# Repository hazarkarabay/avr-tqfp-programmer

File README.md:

Program TQFP AVR's easily without soldering
=====================

So, you designed a board that incorporates a SMD AVR and forgot to break out ISP pins. How you gonna upload your code/(if you have serial pins available)bootloader on your microcontroller?

This was my problem. Instead of adding test points to relevant signals, reordering PCBs and messing with pogo pins, I preprogrammed the chips using a TQFP adapter. Here's how I do it.

### You'll need:
- An AVR ISP programmer. You can use a dedicated programmer (Atmel MKII, Atmel ICE3, USBasp etc.) or you can use an Arduino as ISP. If you are not sure, read here: https://learn.sparkfun.com/tutorials/installing-an-arduino-bootloader
- A TQFP to DIP adapter. [I'm using this.](https://www.aliexpress.com/item/Free-shipping-Chip-programmer-TQFP32-QFP32-LQFP32-TO-DIP28-adapter-socket-support-ATMEGA8-series-TL866A-TL866CS/1969735009.html?aff_platform=ae-aff-deeplink&cpt=1499865009701&sk=UznmeyJee&aff_trace_key=a9dd8dea9e4f4ac5bc85a772afb82508-1499865009701-08514-UznmeyJee)
- ISP to TQFP-DIP adapter board. This board goes between your ISP programmer and TQFP adapter. You can get the adapter board from [pcbs.io](https://PCBs.io/share/r1D3D) or make the board with files provided in this repo and using your favorite method (toner transfer, photoresist etc.)

<a href="https://PCBs.io/share/r1D3D"></img></a>

If you prefer using another PCB manufacturer, feel free to use provided Gerber files.
- AVRDUDE - http://www.nongnu.org/avrdude/

_If your programmer has a ZIF socket (like most Chinese programmers), you don't need that adapter board, you can directly put the TQFP-DIP adapter to your programmers' ZIF socket._    

### How to program your device:
The exact `avrdude` command varies with your programmer and chip type. `avrdude` is a fairly flexible and powerful utility, **please** don't blindly copy/paste the commands provided below, read the `avrdude` manual beforehand. **You can disable your chip with `avrdude` if you mess up fuses and don't know what are you doing.**

>*Word on __disabling__: You can effectively disable the ISP interface **while using** an ISP programmer. If you do this, you can't program your chip over ISP anymore, and it appears [dead](https://hydra-media.cursecdn.com/dota2.gamepedia.com/b/b6/Chatwheel_all_dead.wav). You'll need a real (i.e. high voltage) programmer for restoring at this point (in some situations avrdude can fix that, but do not rely on it). Please don't mess with debugWIRE and RESET fuses if you don't know it. More information can be found at http://www.avrfreaks.net/forum/tutsoft-recovering-locked-out-avr*

After you connect your ISP programmer and adapter, you are ready to program your chip with `avrdude`.
Here is the valid command for **ATMega328P and USBasp** programmer.
```
avrdude -v -patmega328p -cusbasp -e -Ulock:w:0x3F:m -Uefuse:w:0x04:m -Uhfuse:w:0xDE:m -Ulfuse:w:0xFF:m -B100
avrdude -v -patmega328p -cusbasp -e -Ulock:w:0x0F:m -Uflash:w:yoursoftware-withbootloader.hex:i
```

There is 2 seperate commands. First commands only sets the fuse bits and prepares ATMega328P for the actual programming. It sets the crystal, brownout level, disables any locks and does all of it slowly (-B100), because a factory-new ATMega328P comes with its 1MHz internal clock fuse set and USBasp, by default, tries pushing data faster than 250KHz. (ISP frequency is MCU clock/4.) 

Second command is actually programs your hex file and sets the lock fuse to prevent modifying bootloader in your application. It's important, because if you don't set this; you can overwrite/corrupt your bootloader in your application. If you don't use bootloader, you'll need to modify it by your needs.

>**Lock bits explanation:**
There are "fuse bit calculators" on Internet. Here is a example that explains what is going on within the first command. 
http://eleccelerator.com/fusecalc/fusecalc.php?chip=atmega328p&LOW=FF&HIGH=DE&EXTENDED=04&LOCKBIT=3F

### Batch file
I have a batch file to speed up programming multiple AVR's in order. You can see it working on my video. It is very basic, only has a loop and a counter. It serves to my needs and you should customize it if your needs is different. Note that it can't work out of the box, at least the paths needs to be changed.

### 3D-Printed Case for original PCB
A simple 3d-printed case: https://www.thingiverse.com/thing:4529554

### Extended PCB
This is an extension of the original PCB to make it possible to connect sensors and things for testing. PCB files are found in the EASYEDA folder and the home project for this version is located here: https://easyeda.com/sbsivertsen/avr-tqpf-programmer

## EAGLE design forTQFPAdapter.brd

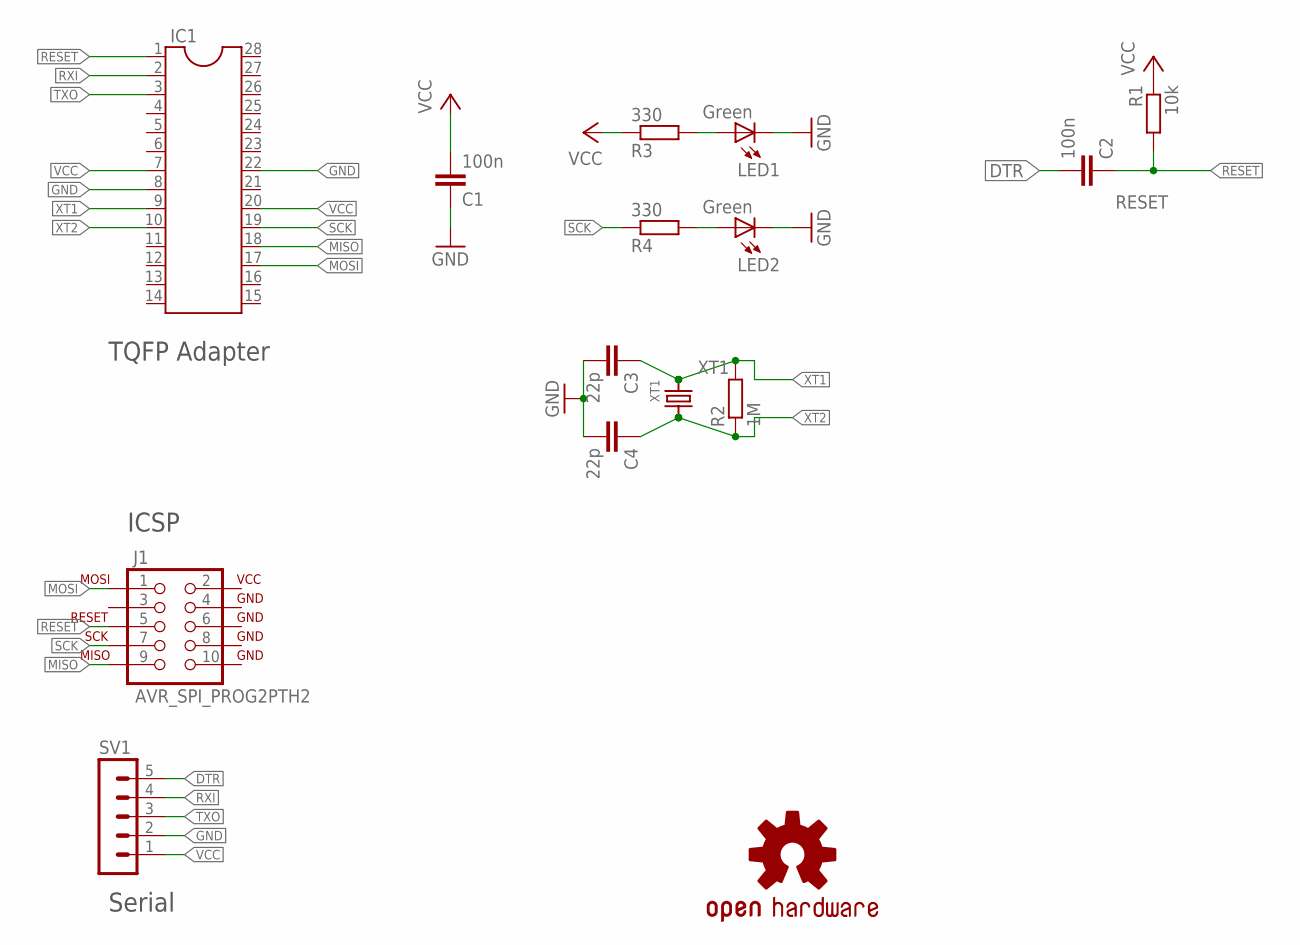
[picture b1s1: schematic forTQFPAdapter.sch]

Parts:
C1, C2: 100n; C0805K
C3, C4: 22p; C0805K
IC1: DIL28; DIL28-6
J1: AVR_SPI_PROG2PTH2; 2X5-SHROUDED
LED1, LED2: Green; LED-1206
LOGO1: OSHW-LOGOM; OSHW-LOGO-M
R1: 10k; M0805
R2: 1M; M0805
R3, R4: 330; M0805
SV1: MA05-1
XT1: CRYSTAL; HC49

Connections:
DTR: C2.2, SV1.5
GND: C1.1, C3.2, C4.2, IC1.8, IC1.22, J1.4 (GND), J1.6 (GND), J1.8 (GND), J1.10 (GND), LED1.C, LED2.C, SV1.2
MISO: IC1.18, J1.9 (MISO)
MOSI: IC1.17, J1.1 (MOSI)
unnamed: LED2.A, R4.2
unnamed: LED1.A, R3.2
RESET: C2.1, IC1.1, J1.5 (RESET), R1.2
RXI: IC1.2, SV1.4
SCK: IC1.19, J1.7 (SCK), R4.1
TXO: IC1.3, SV1.3
VCC: C1.2, IC1.7, IC1.20, J1.2 (VCC), R1.1, R3.1, SV1.1
XT1: C3.1, IC1.9, R2.2, XT1.11 (1), XT1.12 (1)
XT2: C4.1, IC1.10, R2.1, XT1.21 (2), XT1.22 (2)

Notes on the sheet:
ICSP
Serial
TQFP Adapter

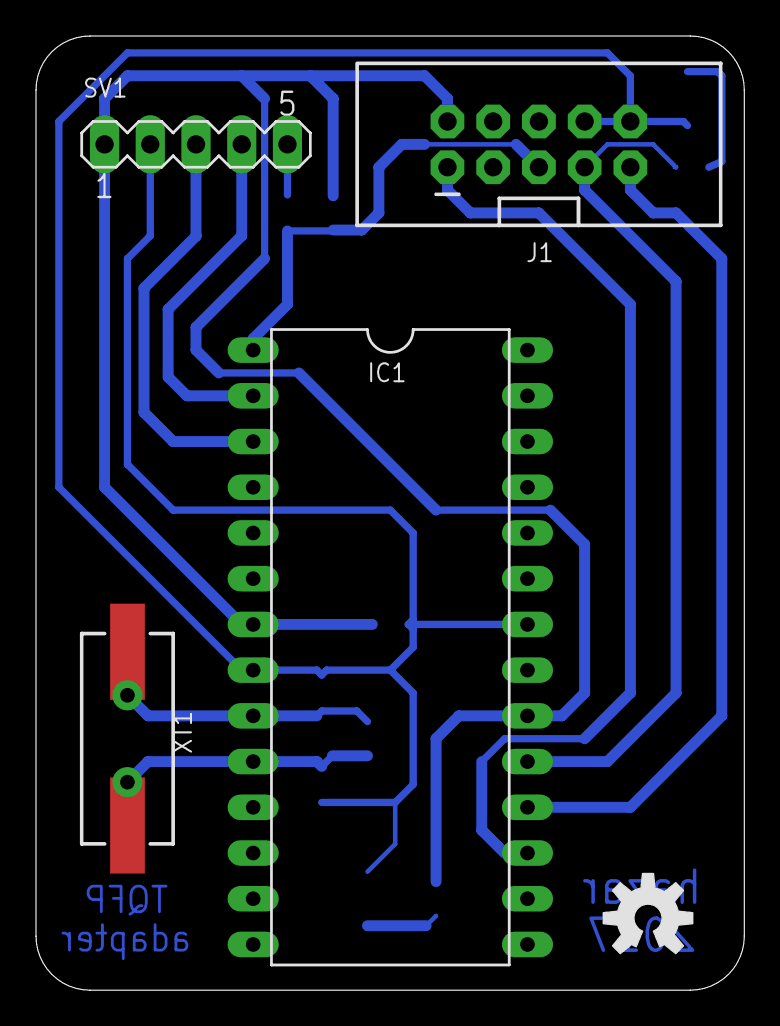
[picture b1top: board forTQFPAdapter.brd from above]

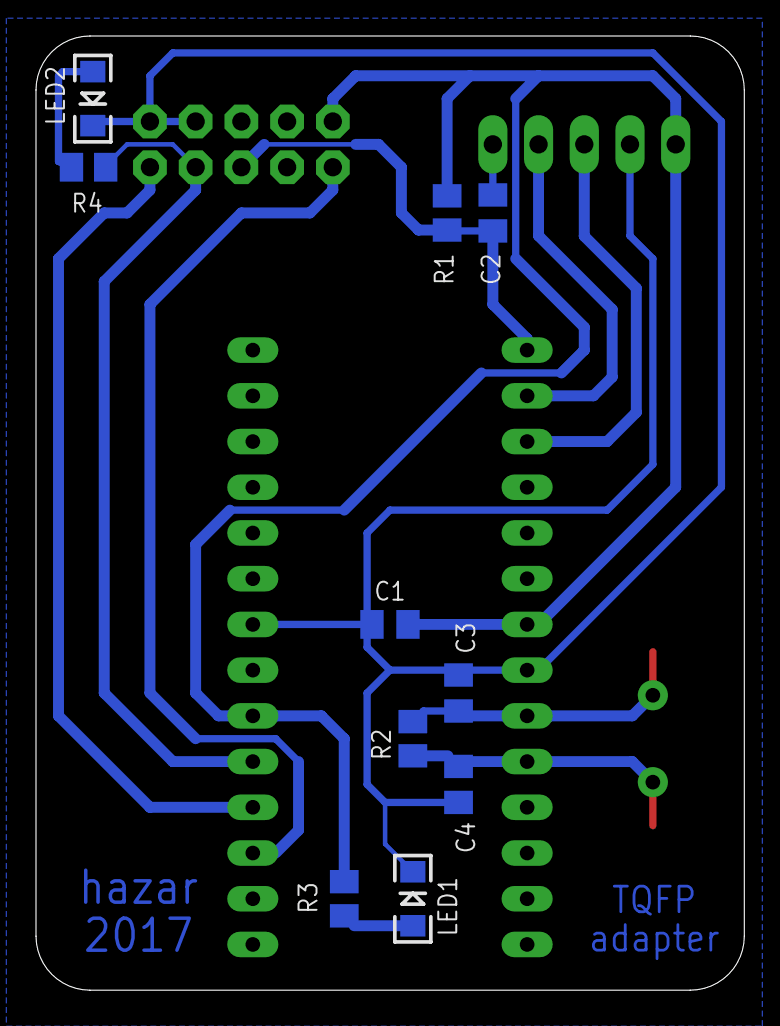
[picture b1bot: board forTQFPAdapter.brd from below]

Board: 2 copper layers, 39.4 x 53.0 mm, 15 parts (10 on the bottom side), 13 nets.

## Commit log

2017-07-12 :boom::camel: Added .gitattributes & .gitignore files
2020-07-08 Added link to a 3d-printed case to README
2020-07-10 Added an extended pcb, created in Easyeda
2020-10-03 Added pictures of extended pcb and updated README file.
2020-10-03 Added AVR programming script

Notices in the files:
parts and their libraries:
SparkFun-Connectors: Licensing: Creative Commons ShareAlike 4.0 International - https://creativecommons.org/licenses/by-sa/4.0
